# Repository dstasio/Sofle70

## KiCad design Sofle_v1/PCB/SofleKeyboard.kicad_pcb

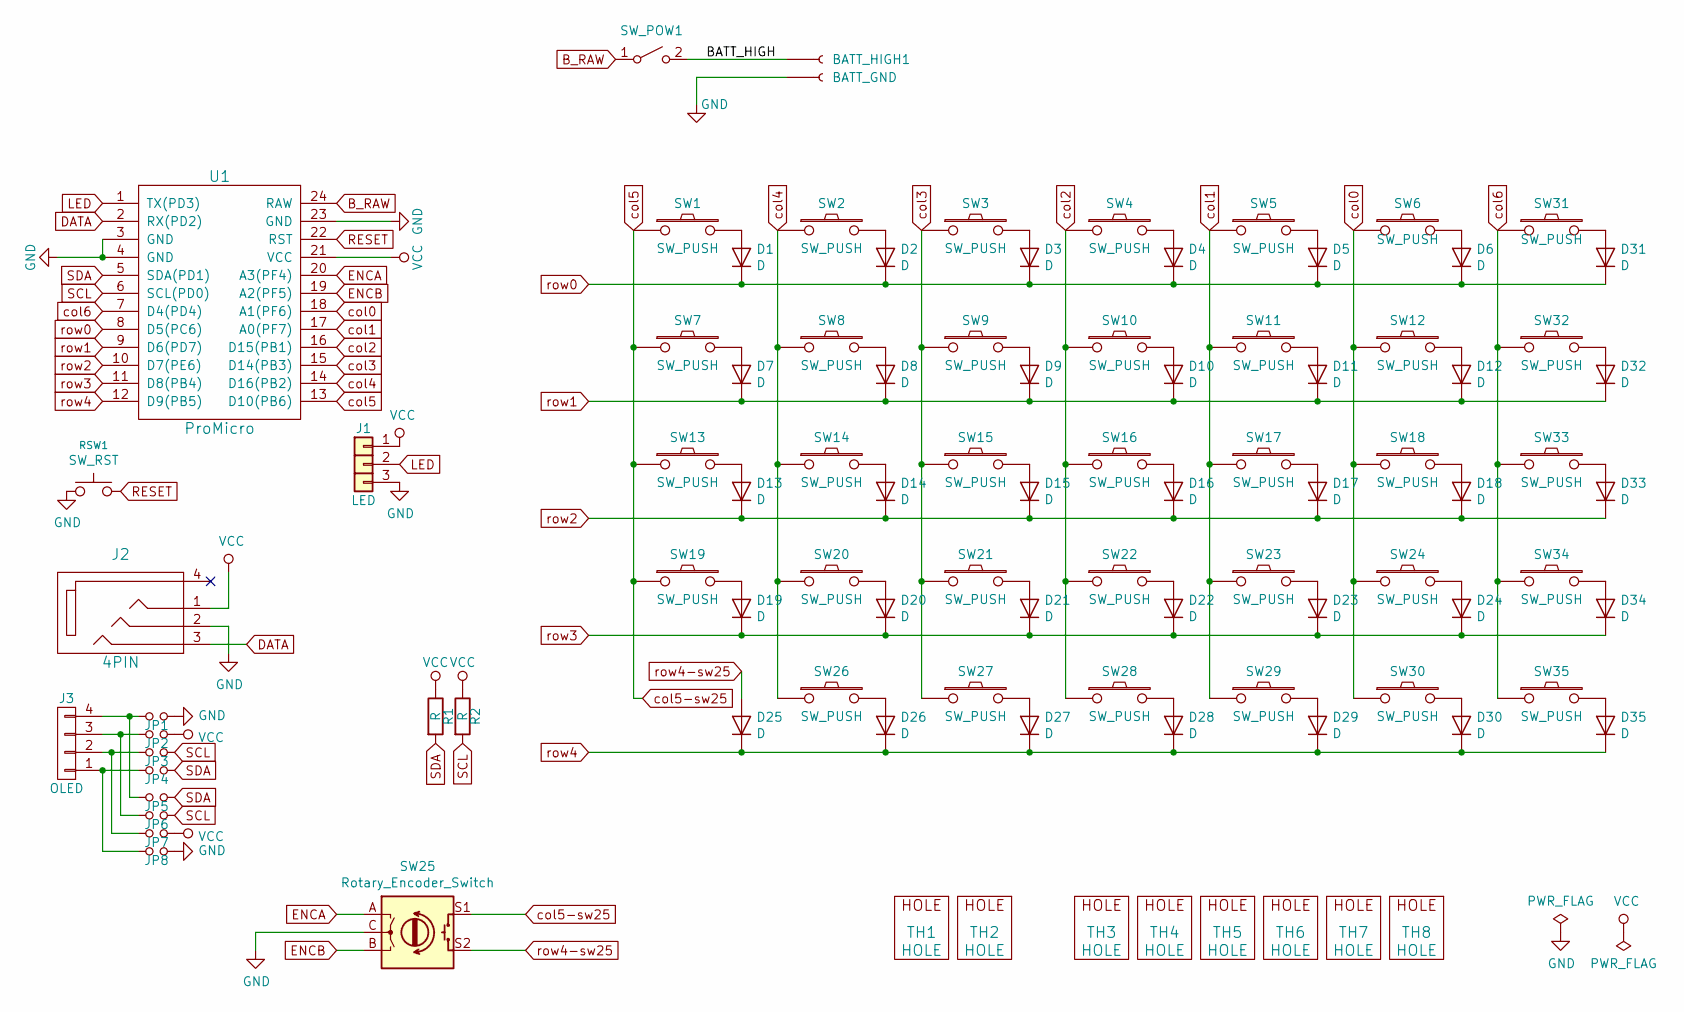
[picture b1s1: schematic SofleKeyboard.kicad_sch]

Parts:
BATT_HIGH1: BATT_GND; Sofle_JST_PH_S2B-PH-K_1x02_P2.00mm_Horizontal
D1, D2, D3, D4, D5, D6, D7, D8, D9, D10, D11, D12, D13, D14, D15, D16, D17, D18, D19, D20, D21, D22, D23, D24, D25, D26, D27, D28, D29, D30, D31, D32, D33, D34, D35: D; Diode_SOD123
J1: LED
J2: 4PIN; MJ-4PP-9
J3: OLED; OLED_4Pin
JP1, JP2, JP3, JP4, JP5, JP6, JP7, JP8: Jumper_NO_Small; Jumper
R1, R2: R; RESISTOR_mini
RSW1: SW_RST; TACT_SWITCH_TVBP06
SW1, SW2, SW3, SW4, SW5, SW6, SW7, SW8, SW9, SW10, SW11, SW12, SW13, SW14, SW15, SW16, SW17, SW18, SW19, SW20, SW21, SW22, SW23, SW24, SW27, SW28, SW29, SW30, SW31, SW32, SW33, SW34, SW35: SW_PUSH; CherryMX_KailhLowProfile_Hotswap
SW25: Rotary_Encoder_Switch; RotaryEncoder_Alps_EC11E-Switch_Vertical_H20mm-keebio_modif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
SW26: SW_PUSH; CherryMX_KailhLowProfile_Hotswap_1.5
SW_POW1: POWER_SWITCH; Sofle_SW_SPDT_PCM12
TH1, TH2: HOLE; M2_HOLE_PCB
TH3, TH4, TH5, TH6, TH7, TH8: HOLE; HOLE_M2_TH
U1: ProMicro

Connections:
/BATT_HIGH: BATT_HIGH1.1, SW_POW1.2 (B)
B_RAW: SW_POW1.1 (A), U1.24 (RAW)
DATA: J2.3, U1.2 (RX(PD2))
ENCA: SW25.A, U1.20 (A3(PF4))
ENCB: SW25.B, U1.19 (A2(PF5))
GND: BATT_HIGH1.2, J1.3, J2.2, JP1.2, JP8.2, RSW1.1, SW25.C, U1.3 (GND), U1.4 (GND), U1.23 (GND)
LED: J1.2, U1.1 (TX(PD3))
unnamed: D1.2 (A), SW1.2
unnamed: D2.2 (A), SW2.2
unnamed: D3.2 (A), SW3.2
unnamed: D4.2 (A), SW4.2
unnamed: D5.2 (A), SW5.2
unnamed: D6.2 (A), SW6.2
unnamed: D7.2 (A), SW7.2
unnamed: D8.2 (A), SW8.2
unnamed: D9.2 (A), SW9.2
unnamed: D10.2 (A), SW10.2
unnamed: D11.2 (A), SW11.2
unnamed: D12.2 (A), SW12.2
unnamed: D13.2 (A), SW13.2
unnamed: D14.2 (A), SW14.2
unnamed: D15.2 (A), SW15.2
unnamed: D16.2 (A), SW16.2
unnamed: D17.2 (A), SW17.2
unnamed: D18.2 (A), SW18.2
unnamed: D19.2 (A), SW19.2
unnamed: D20.2 (A), SW20.2
unnamed: D21.2 (A), SW21.2
unnamed: D22.2 (A), SW22.2
unnamed: D23.2 (A), SW23.2
unnamed: D24.2 (A), SW24.2
unnamed: D26.2 (A), SW26.2
unnamed: D27.2 (A), SW27.2
unnamed: D28.2 (A), SW28.2
unnamed: D29.2 (A), SW29.2
unnamed: D30.2 (A), SW30.2
unnamed: D31.2 (A), SW31.2
unnamed: D32.2 (A), SW32.2
unnamed: D33.2 (A), SW33.2
unnamed: D34.2 (A), SW34.2
unnamed: D35.2 (A), SW35.2
unnamed: J3.1, JP4.1, JP8.1
unnamed: J3.2, JP3.1, JP7.1
unnamed: J3.3, JP2.1, JP6.1
unnamed: J3.4, JP1.1, JP5.1
RESET: RSW1.2, U1.22 (RST)
SCL: JP3.2, JP6.2, R2.2, U1.6 (SCL(PD0))
SDA: JP4.2, JP5.2, R1.2, U1.5 (SDA(PD1))
VCC: J1.1, J2.1, JP2.2, JP7.2, R1.1, R2.1, U1.21 (VCC)
col0: SW6.1, SW12.1, SW18.1, SW24.1, SW30.1, U1.18 (A1(PF6))
col1: SW5.1, SW11.1, SW17.1, SW23.1, SW29.1, U1.17 (A0(PF7))
col2: SW4.1, SW10.1, SW16.1, SW22.1, SW28.1, U1.16 (D15(PB1))
col3: SW3.1, SW9.1, SW15.1, SW21.1, SW27.1, U1.15 (D14(PB3))
col4: SW2.1, SW8.1, SW14.1, SW20.1, SW26.1, U1.14 (D16(PB2))
col5: SW1.1, SW7.1, SW13.1, SW19.1, SW25.S1, U1.13 (D10(PB6))
col6: SW31.1, SW32.1, SW33.1, SW34.1, SW35.1, U1.7 (D4(PD4))
row0: D1.1 (K), D2.1 (K), D3.1 (K), D4.1 (K), D5.1 (K), D6.1 (K), D31.1 (K), U1.8 (D5(PC6))
row1: D7.1 (K), D8.1 (K), D9.1 (K), D10.1 (K), D11.1 (K), D12.1 (K), D32.1 (K), U1.9 (D6(PD7))
row2: D13.1 (K), D14.1 (K), D15.1 (K), D16.1 (K), D17.1 (K), D18.1 (K), D33.1 (K), U1.10 (D7(PE6))
row3: D19.1 (K), D20.1 (K), D21.1 (K), D22.1 (K), D23.1 (K), D24.1 (K), D34.1 (K), U1.11 (D8(PB4))
row4: D25.1 (K), D26.1 (K), D27.1 (K), D28.1 (K), D29.1 (K), D30.1 (K), D35.1 (K), U1.12 (D9(PB5))
row4-sw25: D25.2 (A), SW25.S2

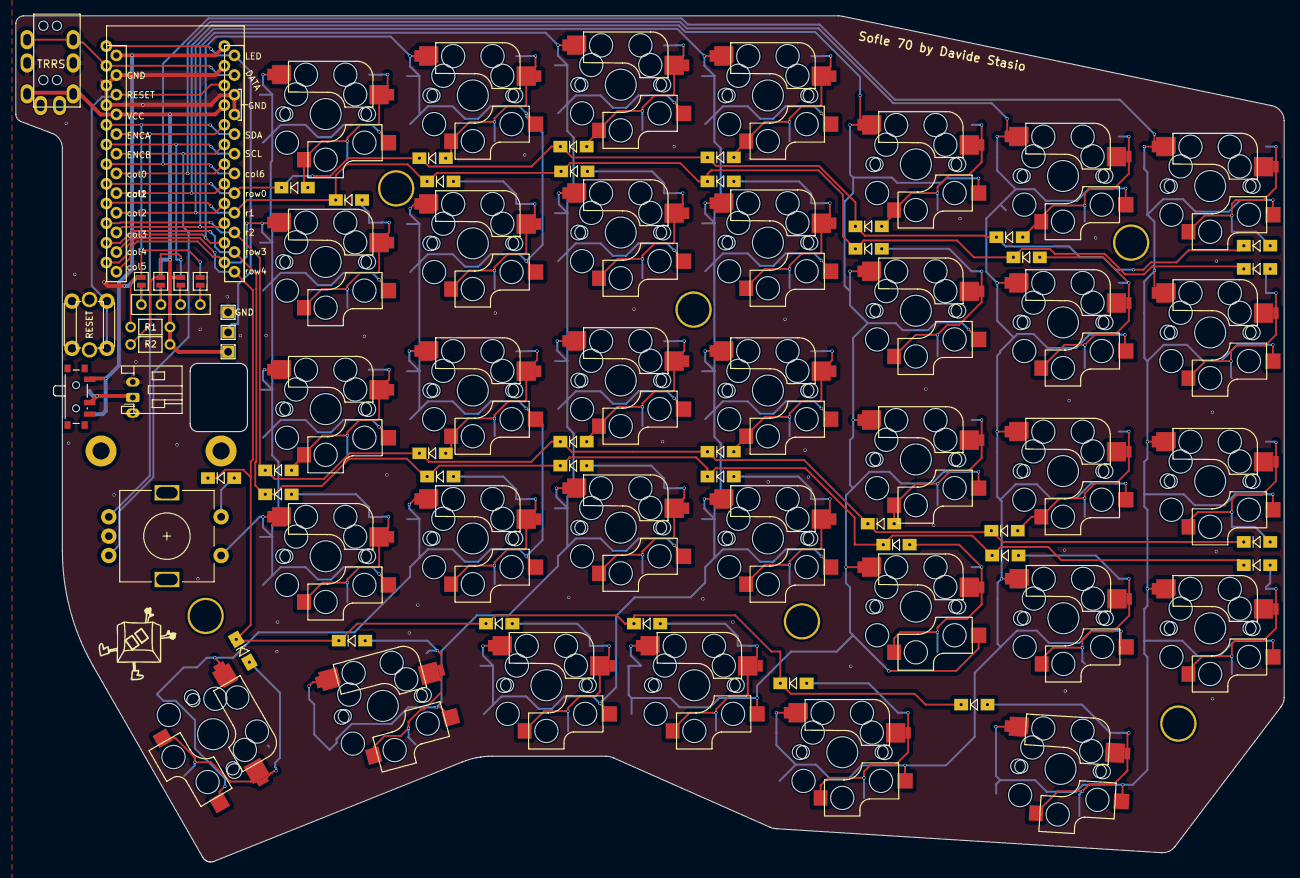
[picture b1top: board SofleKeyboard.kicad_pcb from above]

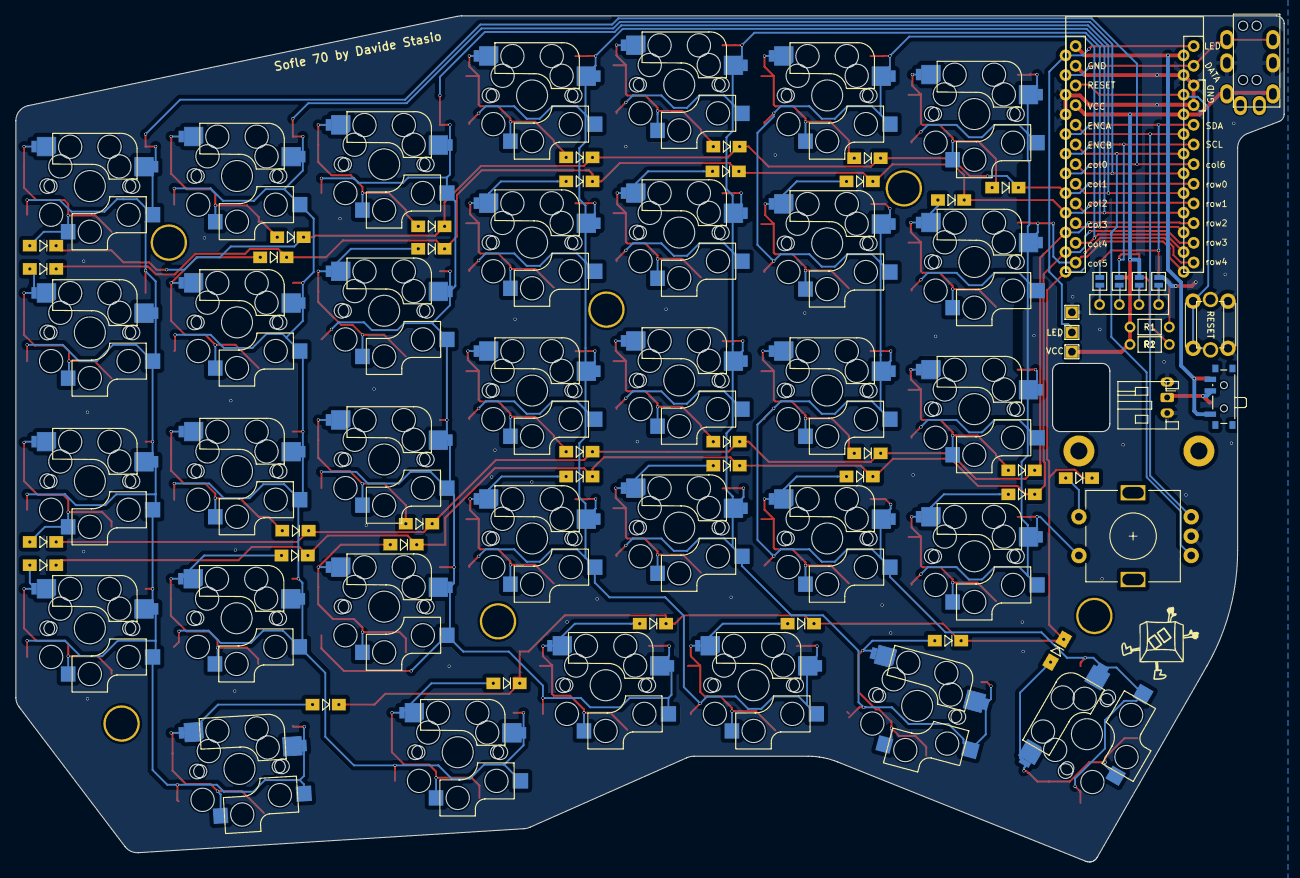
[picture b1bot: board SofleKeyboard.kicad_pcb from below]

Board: 2 copper layers, 163.8 x 109.2 mm, 97 parts (5 on the bottom side), 62 nets.

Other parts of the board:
Ref**: Val**; SofleLogoSmall
Ref**#2: Val**; SofleLogoSmall

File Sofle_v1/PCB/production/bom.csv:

Designator,Footprint,Quantity,Value,LCSC Part #
BATT_HIGH1,Sofle_JST_PH_S2B-PH-K_1x02_P2.00mm_Horizontal,1,BATT_GND,
"D1, D10, D11, D12, D13, D14, D15, D16, D17, D18, D19, D2, D20, D21, D22, D23, D24, D25, D26, D27, D28, D29, D3, D30, D31, D32, D33, D34, D35, D4, D5, D6, D7, D8, D9",Diode_SOD123,35,D,
J1,LED,1,LED,
J2,MJ-4PP-9,1,4PIN,
J3,OLED_4Pin,1,OLED,
"JP1, JP2, JP3, JP4, JP5, JP6, JP7, JP8",Jumper,8,Jumper_NO_Small,
"R1, R2",RESISTOR_mini,2,R,
RSW1,Sofle_Tactile Switch,1,SW_RST,
"SW1, SW10, SW11, SW12, SW13, SW14, SW15, SW16, SW17, SW18, SW19, SW2, SW20, SW21, SW22, SW23, SW24, SW27, SW28, SW29, SW3, SW30, SW31, SW32, SW33, SW34, SW35, SW4, SW5, SW6, SW7, SW8, SW9",CherryMX_KailhLowProfile_Hotswap,33,SW_PUSH,
SW25,RotaryEncoder_Alps_EC11E-Switch_Vertical_H20mm-keebio_modified,1,Rotary_Encoder_Switch,
SW26,CherryMX_KailhLowProfile_Hotswap_1.5,1,SW_PUSH,
SW_POW1,Sofle_SW_SPDT_PCM12,1,POWER_SWITCH,
"TH1, TH2",M2_HOLE_PCB,2,HOLE,
"TH3, TH4, TH5, TH6, TH7, TH8",HOLE_M2_TH,6,HOLE,
U1,ProMicro,1,ProMicro,

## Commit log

2025-08-12 Added Column 6
2025-08-15 Cleanup
2025-08-17 Moved TRRS + battery connector.
2025-08-17 Plates.
2025-08-17 JLCPCB export.
2025-08-30 Bugfixes.
